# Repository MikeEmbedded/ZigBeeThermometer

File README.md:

<h1 align="center">ZigBee Thermometer</h1>

## Description

**Based on CC2530/nRF52833 and eInk Display Zigbee Thermometer**

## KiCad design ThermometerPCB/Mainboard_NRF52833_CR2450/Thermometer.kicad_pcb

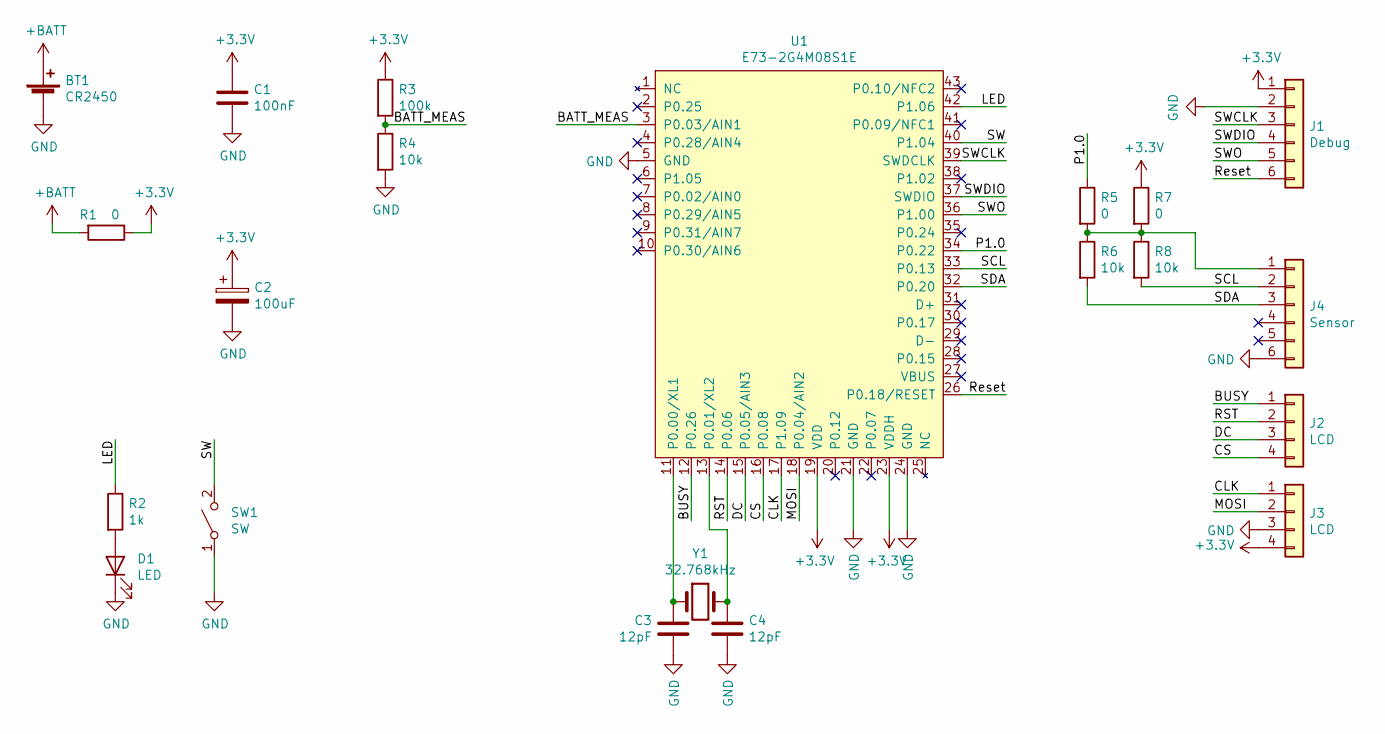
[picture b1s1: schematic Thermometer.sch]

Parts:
BT1: CR2450; BatteryHolder_Keystone_3008_1x2450
C1: 100nF; C_0603_1608Metric
C2: 100uF; CP_EIA-3528-15_AVX-H
C3, C4: 12pF; C_0603_1608Metric
D1: LED; LED_0805_2012Metric
J1: Debug; PinHeader_1x06_P1.27mm_Vertical
J2, J3: LCD; PinHeader_1x04_P1.27mm_Vertical
J4: Sensor; PinHeader_1x06_P1.27mm_Vertical
R1, R5, R7: 0; R_0805_2012Metric
R2: 1k; R_0805_2012Metric
R3: 100k; R_0805_2012Metric
R4, R6, R8: 10k; R_0805_2012Metric
SW1: SW; Panasonic_EVQPUL_EVQPUC
U1: E73-2G4M08S1E
Y1: 32.768kHz; Crystal_SMD_MicroCrystal_CC8V-T1A-2Pin_2.0x1.2mm_HandSolder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

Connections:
+3V3: C1.1, C2.1, J1.1, J3.4, R1.1, R3.1, R7.1, U1.19 (VDD), U1.23 (VDDH)
+BATT: BT1.1 (+), R1.2
/BATT_MEAS: R3.2, R4.1, U1.3 (P0.03/AIN1)
/BUSY: J2.1, U1.12 (P0.26)
/CLK: J3.1, U1.17 (P1.09)
/CS: J2.4, U1.16 (P0.08)
/DC: J2.3, U1.15 (P0.05/AIN3)
/LED: R2.1, U1.42 (P1.06)
/MOSI: J3.2, U1.18 (P0.04/AIN2)
/P1.0: R5.1, U1.34 (P0.22)
/RST: J2.2, U1.14 (P0.06)
/Reset: J1.6, U1.26 (P0.18/RESET)
/SCL: J4.2, R8.2, U1.33 (P0.13)
/SDA: J4.3, R6.2, U1.32 (P0.20)
/SW: SW1.2 (B), U1.40 (P1.04)
/SWCLK: J1.3, U1.39 (SWDCLK)
/SWDIO: J1.4, U1.37 (SWDIO)
/SWO: J1.5, U1.36 (P1.00)
GND: BT1.2 (-), C1.2, C2.2, C3.2, C4.2, D1.1 (K), J1.2, J3.3, J4.6, R4.2, SW1.1 (A), U1.5 (GND), U1.21 (GND), U1.24 (GND)
unnamed: C3.1, U1.11 (P0.00/XL1), Y1.1
unnamed: C4.1, U1.13 (P0.01/XL2), Y1.2
unnamed: D1.2 (A), R2.2
unnamed: J4.1, R5.2, R6.1, R7.2, R8.1

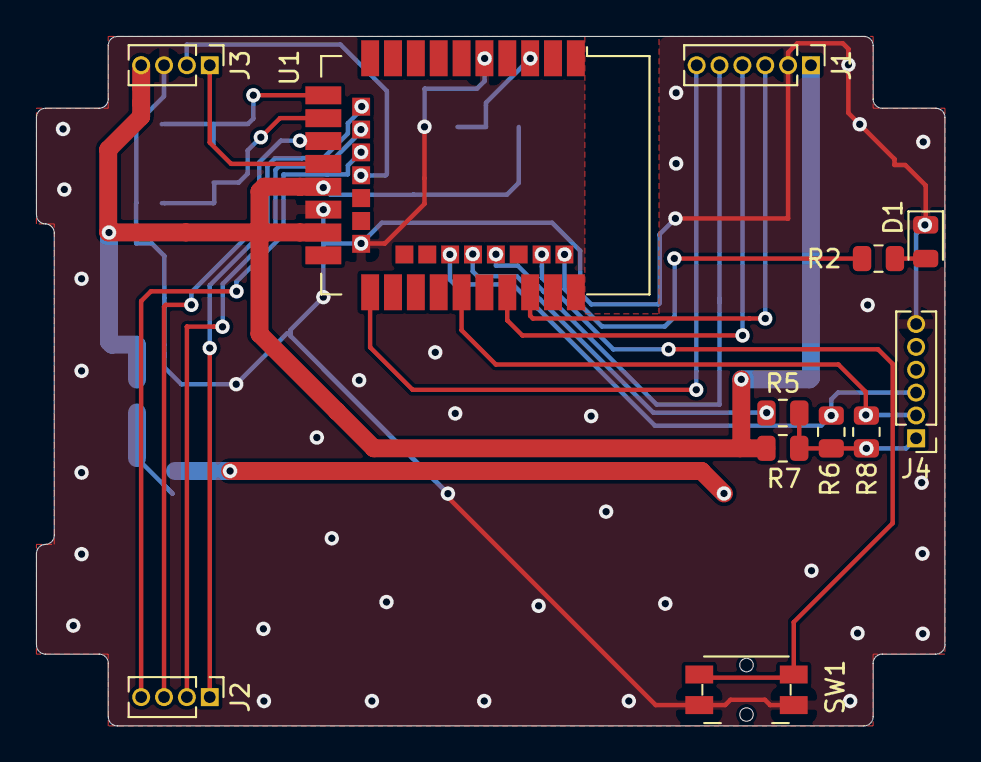
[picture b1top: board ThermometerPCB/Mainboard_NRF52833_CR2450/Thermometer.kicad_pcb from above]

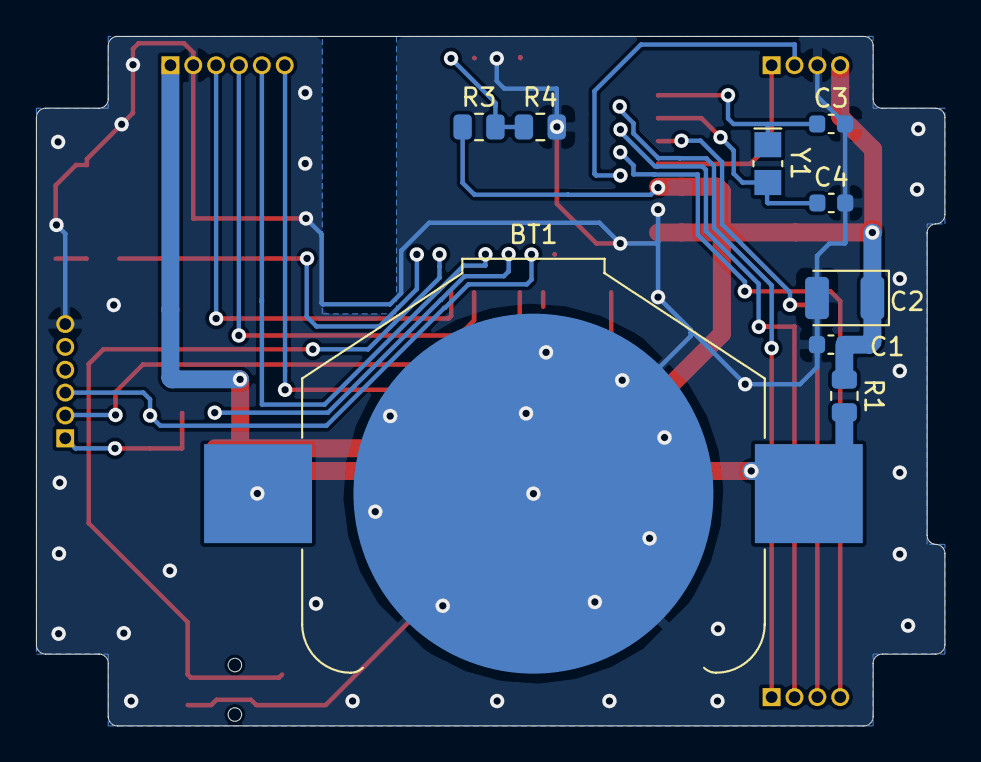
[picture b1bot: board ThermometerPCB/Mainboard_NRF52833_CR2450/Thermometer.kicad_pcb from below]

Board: 2 copper layers, 50.5 x 38.3 mm, 21 parts (9 on the bottom side), 23 nets.

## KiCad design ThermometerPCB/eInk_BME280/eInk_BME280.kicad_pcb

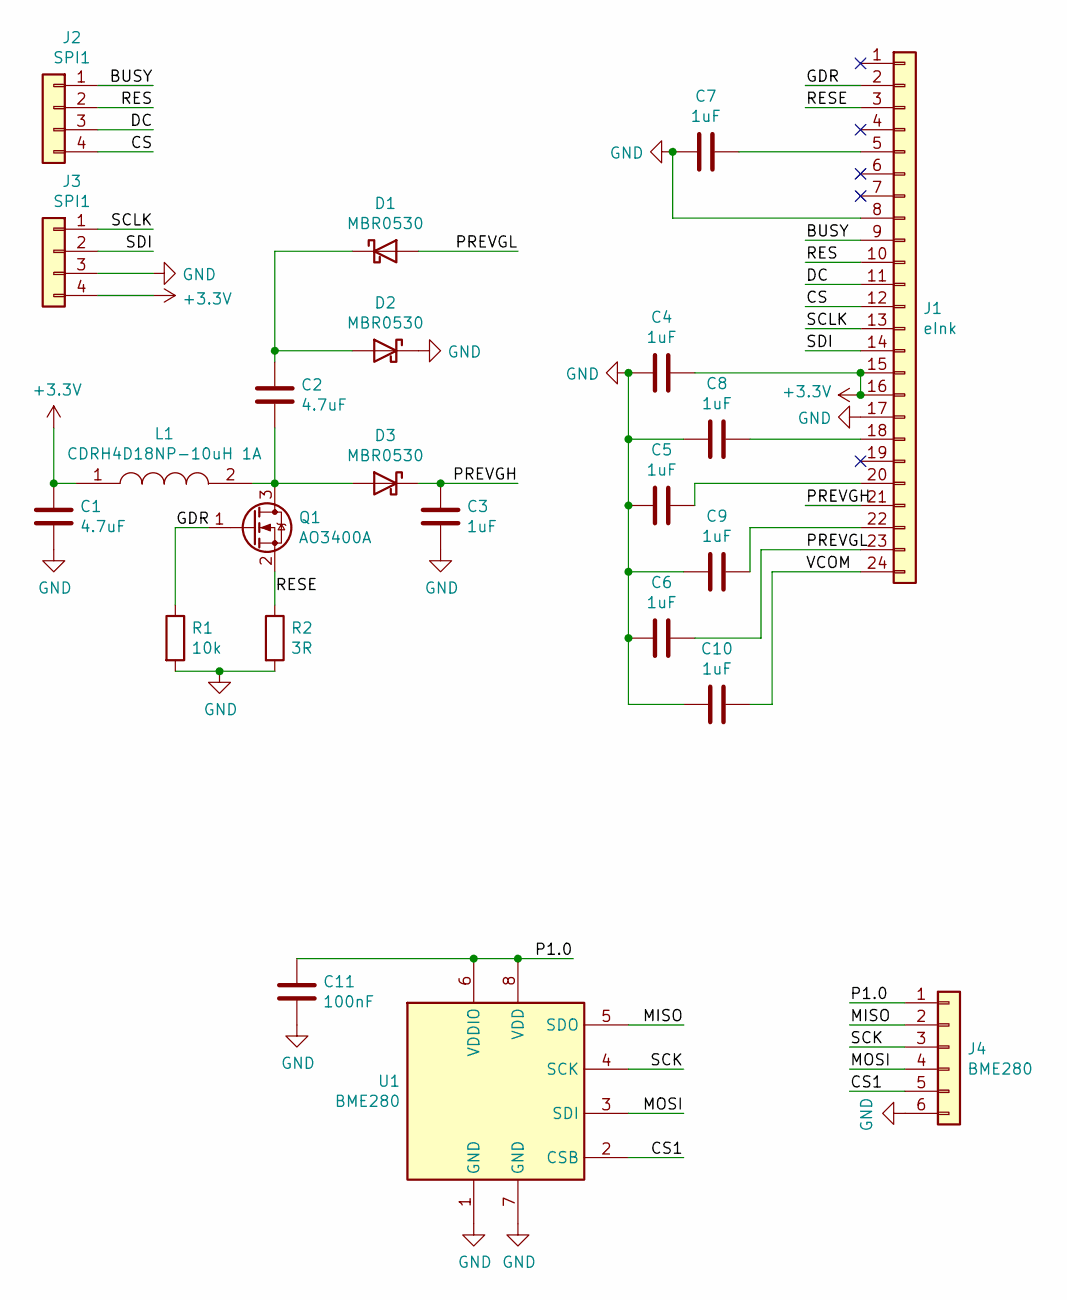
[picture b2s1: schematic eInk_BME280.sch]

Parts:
C1, C2: 4.7uF; C_0603_1608Metric
C3, C4, C5, C6, C7, C8, C9, C10: 1uF; C_0603_1608Metric
C11: 100nF; C_0603_1608Metric
D1, D2, D3: MBR0530; D_SOD-123
J1: eInk; FPC-0.5-24P
J2, J3: SPI1; PinHeader_1x04_P1.27mm_Vertical
J4: BME280; PinHeader_1x06_P1.27mm_Vertical
L1: CDRH4D18NP-10uH 1A; CDRH4D18NP100NC; Manufacturer_Part_Number CDRH4D18NP-2R2NC; Mouser Part Number 851-CDRH4D18NP-2R2NC
Q1: AO3400A; SOT-23
R1: 10k; R_0603_1608Metric
R2: 3R; R_0603_1608Metric
U1: BME280; Bosch_LGA-8_2.5x2.5mm_P0.65mm_ClockwisePinNumbering

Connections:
+3V3: C1.1, C4.1, J1.15, J1.16, J3.4, L1.1
/BUSY: J1.9, J2.1
/CS: J1.12, J2.4
/CS1: J4.5, U1.2 (CSB)
/DC: J1.11, J2.3
/GDR: J1.2, Q1.1 (G), R1.1
/MISO: J4.2, U1.5 (SDO)
/MOSI: J4.4, U1.3 (SDI)
/P1.0: C11.1, J4.1, U1.6 (VDDIO), U1.8 (VDD)
/PREVGH: C3.1, D3.1 (K), J1.21
/PREVGL: C6.1, D1.2 (A), J1.23
/RES: J1.10, J2.2
/RESE: J1.3, Q1.2 (S), R2.1
/SCK: J4.3, U1.4 (SCK)
/SCLK: J1.13, J3.1
/SDI: J1.14, J3.2
/VCOM: C10.1, J1.24
GND: C1.2, C3.2, C4.2, C5.2, C6.2, C7.2, C8.2, C9.2, C10.2, C11.2, D2.1 (K), J1.8, J1.17, J3.3, J4.6, R1.2, R2.2, U1.1 (GND), U1.7 (GND)
unnamed: C2.1, D1.1 (K), D2.2 (A)
unnamed: C2.2, D3.2 (A), L1.2, Q1.3 (D)
unnamed: C5.1, J1.20
unnamed: C7.1, J1.5
unnamed: C8.1, J1.18
unnamed: C9.1, J1.22

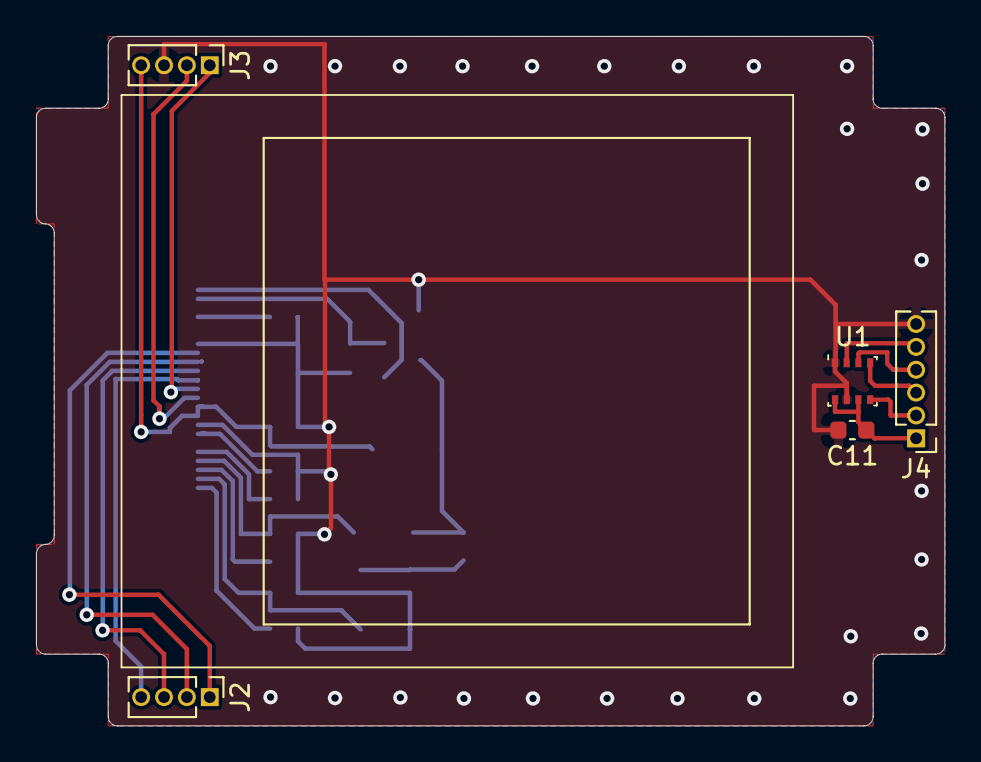
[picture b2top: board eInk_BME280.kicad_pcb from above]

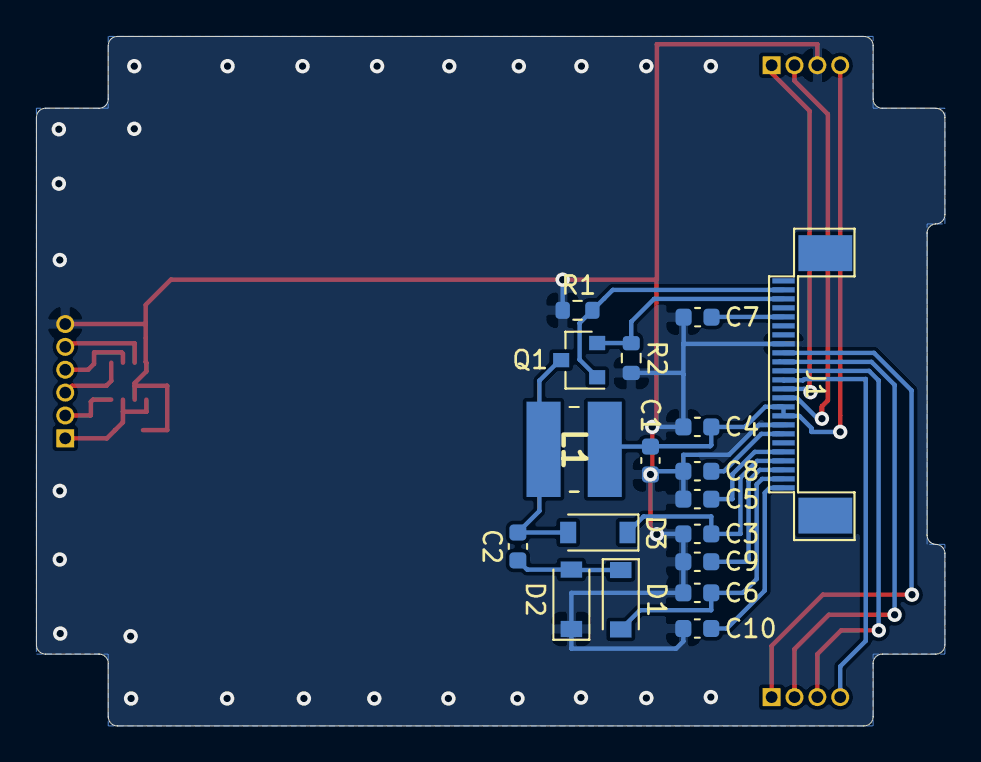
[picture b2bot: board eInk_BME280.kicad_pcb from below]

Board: 2 copper layers, 50.5 x 38.3 mm, 23 parts (18 on the bottom side), 24 nets.

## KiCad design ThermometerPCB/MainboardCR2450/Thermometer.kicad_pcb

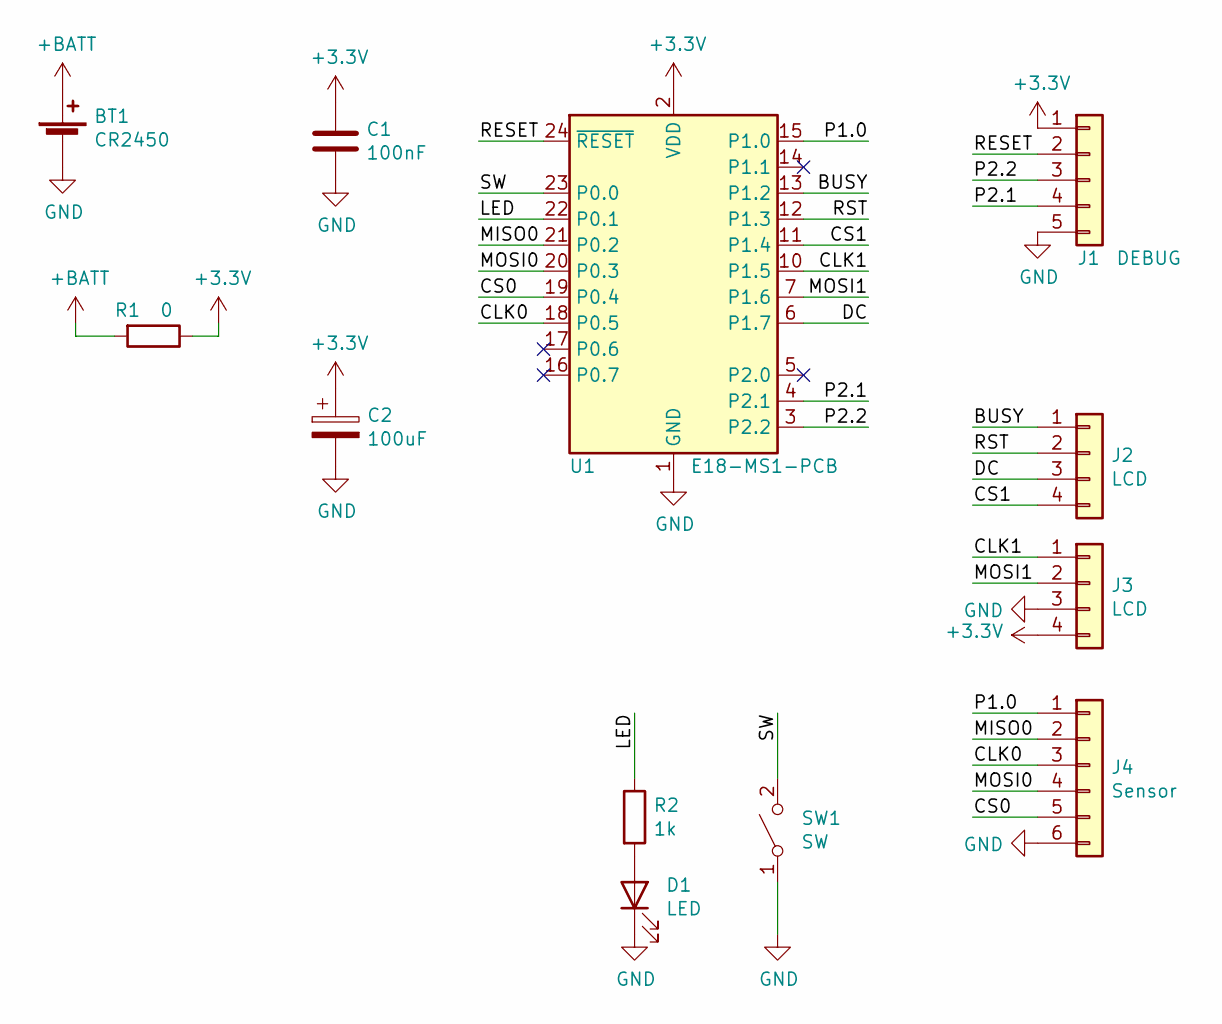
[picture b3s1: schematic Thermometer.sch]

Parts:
BT1: CR2450; BatteryHolder_Keystone_3008_1x2450
C1: 100nF; C_0603_1608Metric
C2: 100uF; CP_EIA-3528-15_AVX-H
D1: LED; LED_0805_2012Metric
J1: DEBUG; PinHeader_1x05_P2.54mm_Vertical
J2, J3: LCD; PinHeader_1x04_P1.27mm_Vertical
J4: Sensor; PinHeader_1x06_P1.27mm_Vertical
R1: 0; R_0805_2012Metric
R2: 1k; R_0805_2012Metric
SW1: SW; Panasonic_EVQPUL_EVQPUC
U1: E18-MS1-PCB

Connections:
+3V3: C1.1, C2.1, J1.1, J3.4, R1.1, U1.2 (VDD)
+BATT: BT1.1 (+), R1.2
/BUSY: J2.1, U1.13 (P1.2)
/CLK0: J4.3, U1.18 (P0.5)
/CLK1: J3.1, U1.10 (P1.5)
/CS0: J4.5, U1.19 (P0.4)
/CS1: J2.4, U1.11 (P1.4)
/DC: J2.3, U1.6 (P1.7)
/LED: R2.1, U1.22 (P0.1)
/MISO0: J4.2, U1.21 (P0.2)
/MOSI0: J4.4, U1.20 (P0.3)
/MOSI1: J3.2, U1.7 (P1.6)
/P1.0: J4.1, U1.15 (P1.0)
/P2.1: J1.4, U1.4 (P2.1)
/P2.2: J1.3, U1.3 (P2.2)
/RESET: J1.2, U1.24 (~RESET)
/RST: J2.2, U1.12 (P1.3)
/SW: SW1.2 (B), U1.23 (P0.0)
GND: BT1.2 (-), C1.2, C2.2, D1.1 (K), J1.5, J3.3, J4.6, SW1.1 (A), U1.1 (GND)
unnamed: D1.2 (A), R2.2

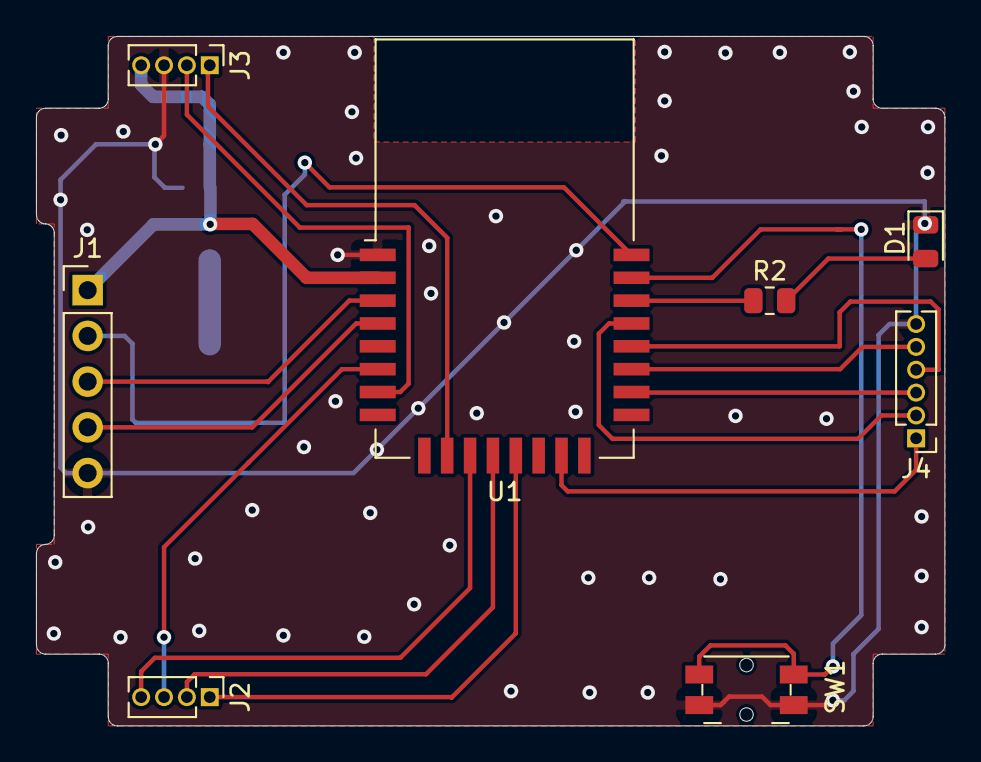
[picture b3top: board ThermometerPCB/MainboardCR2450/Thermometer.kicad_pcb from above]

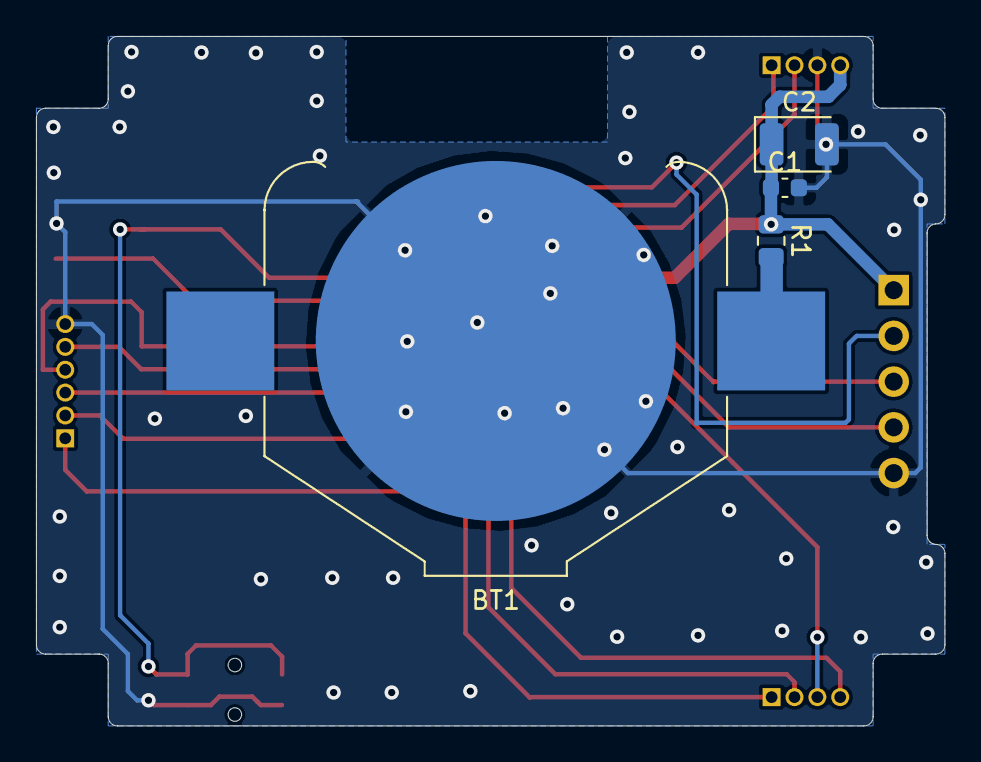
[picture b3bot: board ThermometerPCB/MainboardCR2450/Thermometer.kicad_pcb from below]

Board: 2 copper layers, 50.5 x 38.3 mm, 12 parts (4 on the bottom side), 20 nets.

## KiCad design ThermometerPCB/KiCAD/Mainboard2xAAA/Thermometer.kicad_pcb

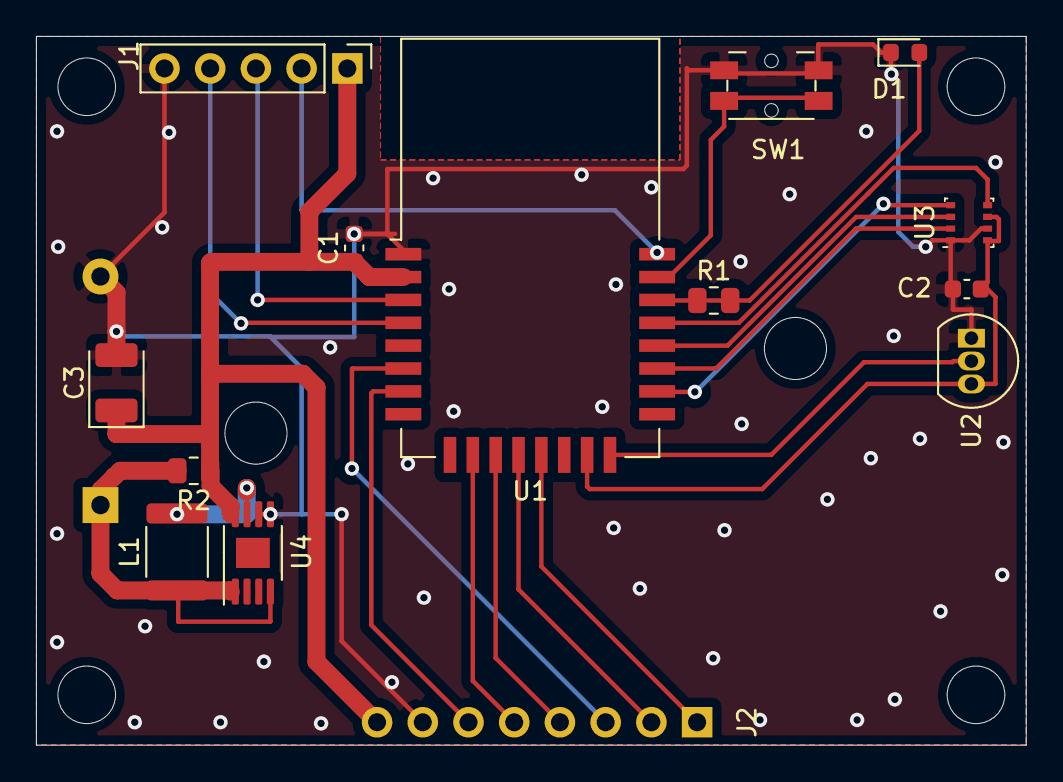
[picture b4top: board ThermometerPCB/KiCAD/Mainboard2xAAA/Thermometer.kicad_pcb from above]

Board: 2 copper layers, 55.0 x 39.4 mm, 15 parts (1 on the bottom side), 22 nets.

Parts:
BT1: Battery; BatteryHolder_Keystone_2468_2xAAA
C1, C2: 100nF; C_0603_1608Metric
C3: 10uF; CP_EIA-3528-15_AVX-H
D1: LED; LED_0603_1608Metric
J1: DEBUG; PinHeader_1x05_P2.54mm_Vertical
J2: LCD; PinSocket_1x08_P2.54mm_Vertical
L1: 47uH; L_1812_4532Metric
R1: 1k; R_0805_2012Metric
R2: 0; R_0805_2012Metric
SW1: SW; Panasonic_EVQPUL_EVQPUC
U1: E18-MS1-PCB
U2: DS18B20; TO-92_Inline
U3: BME280; Bosch_LGA-8_2.5x2.5mm_P0.65mm_ClockwisePinNumbering
U4: MAX1678; MSOP-8-1EP_3x3mm_P0.65mm_EP1.68x1.88mm

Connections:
+3V3: C1.1, C3.1, J1.1, J2.8, R2.1, U1.2, U4.8
+BATT: BT1.1, L1.1, R2.2, U4.1, U4.4
/BUSY: J2.1, U1.13
/CLK0: U1.18, U3.4
/CLK1: J2.5, U1.10
/CS0: U1.19, U3.2
/CS1: J2.4, U1.11
/DC: J2.3, U1.6
/DQ: U1.16, U2.2
/LED: R1.1, U1.22
/MISO0: U1.21, U3.5
/MOSI0: U1.20, U3.3
/MOSI1: J2.6, U1.7
/P1.0: C2.1, U1.15, U2.3, U3.6, U3.8
/P2.1: J1.4, U1.4
/P2.2: J1.3, U1.3
/RESET: J1.2, U1.24
/RST: J2.2, U1.12
/SW: SW1.2, U1.23
GND: BT1.2, C1.2, C2.2, C3.2, D1.1, J1.5, J2.7, SW1.1, U1.1, U2.1, U3.1, U3.7, U4.5, U4.6
unnamed: D1.2, R1.2
unnamed: L1.2, U4.7

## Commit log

2021-05-07 Initial Upload
2021-05-27 New PCB Uploads
2021-05-30 nrf52833 Upload
2021-06-20 NRF52833 board update
